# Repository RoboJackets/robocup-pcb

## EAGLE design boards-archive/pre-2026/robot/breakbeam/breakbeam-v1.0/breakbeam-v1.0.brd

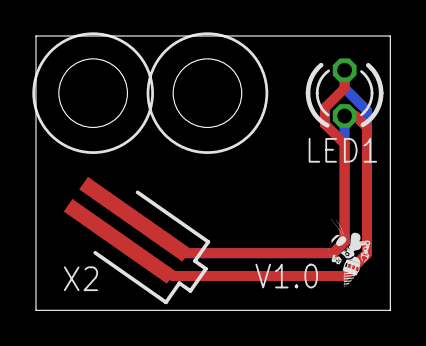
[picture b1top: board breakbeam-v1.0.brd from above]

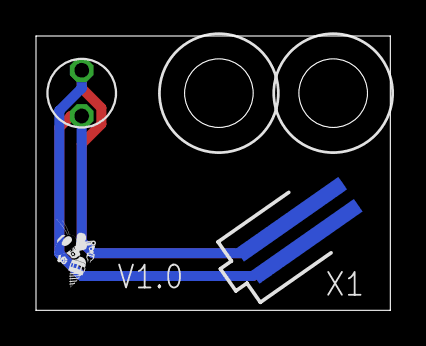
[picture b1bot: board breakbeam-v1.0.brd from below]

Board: 2 copper layers, 19.7 x 15.2 mm, 5 parts (2 on the bottom side), 2 nets.

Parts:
LED1: LED3MM
U$1, U$4: ROBOBUZZ_0.2X
X1, X2: 87438-02

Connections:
unnamed: LED1.A, X1.1, X2.1
unnamed: LED1.K, X1.2, X2.2

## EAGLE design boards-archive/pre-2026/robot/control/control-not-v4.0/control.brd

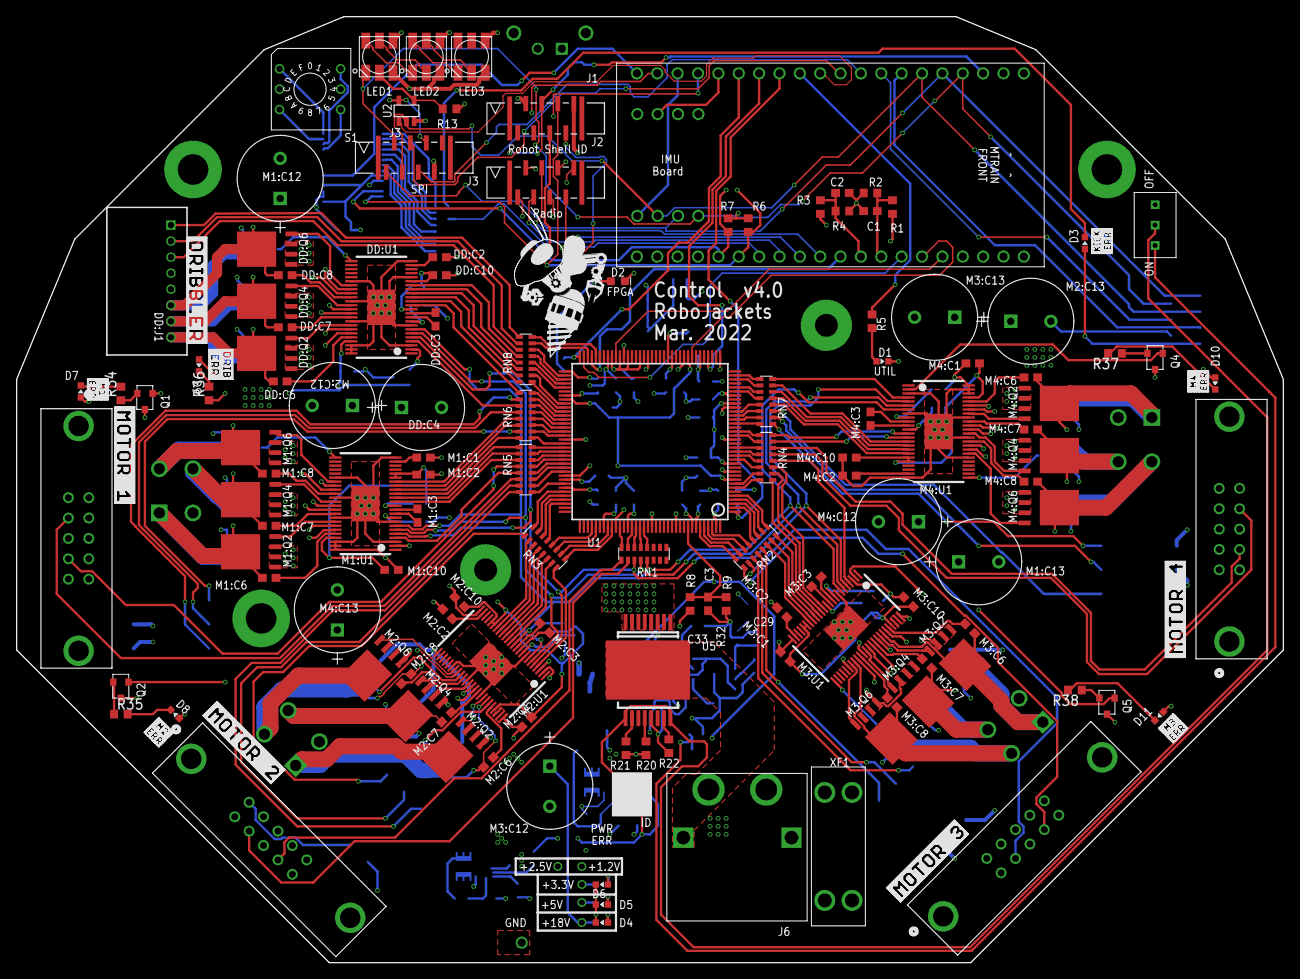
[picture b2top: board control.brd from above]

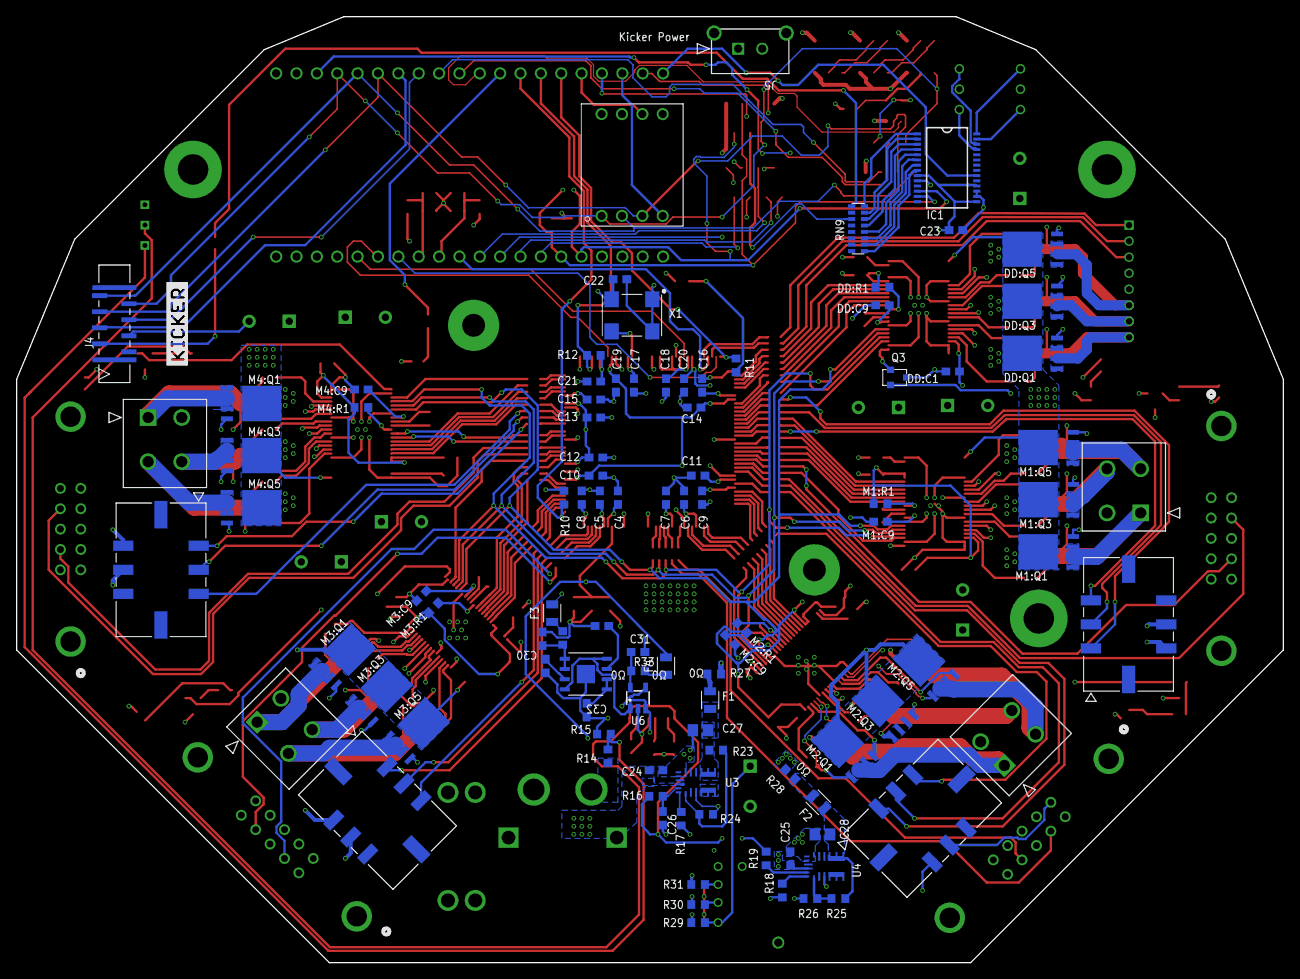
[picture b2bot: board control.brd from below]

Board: 6 copper layers, 158.0 x 118.0 mm, 238 parts (100 on the bottom side), 312 nets.

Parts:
C1: 0.1uF 50V; C0603
C2, C3, C4, C5, C6, C7, C8, C9, C10, C11, C12, C13, C14, C15, C16, C17, C18, C19, C20, C21, C22, C23: 0.1uF; C0603
C24, C25: GRM188R6YA106MA73D; C0603
C26: 2.2uF 50V; C0603
C27, C28: 22uF 16V; C0805
C29: 10uF; C0603
C30, C31, C32, C33: 1uF; C0603
D1: BLUE; CHIP-LED0603
D2: BLUE; LED-0603
D3, D7, D8, D9, D10, D11: RED; CHIP-LED0603
D4, D5, D6: GREEN; CHIP-LED0603
DD:C1, DD:C2: 1uF; C0603
DD:C3: 0.022uF 50V; C0603
DD:C4: ECA-1HHG221; CAP_PAN_10X12.5
DD:C6, DD:C7, DD:C8, DD:C10: 0.1uF 50V; C0603
DD:C9: 2.2uF 50V; C0603
DD:J1: 8-PIN_2MM-H; 2MM-8-H
DD:Q1, DD:Q2, DD:Q3, DD:Q4, DD:Q5, DD:Q6: IRFH7545; PQFN_5X6_E
DD:R1: 10k; R0603
DD:U1: DRV8303DCA; TSSOP-48_PAD
F1, F2, F3, F4: 0805L200SLTHYR; FUSC2113X75
IC1: MCP23017-E/SS; SSOP-28
J1, J2, J3, J4: SFW8S-2STE1LF; CON8_1X8_UB_SFW_JAE
J5: 436500217; CON_436500217_MOL
J6: XT60PW-MAMASS; XT60PW-M
KIT1: MTRAIN; MTRAIN-KIT
KIT2: IMU
LED1, LED2, LED3: APA102C-5050; APA102_5050
M1:C1, M1:C2, M2:C1, M2:C2, M3:C1, M3:C2, M4:C1, M4:C2: 1uF; C0603
M1:C3, M2:C3, M3:C3, M4:C3: 0.022uF 50V; C0603
M1:C6, M1:C7, M1:C8, M1:C10, M2:C6, M2:C7, M2:C8, M2:C10, M3:C6, M3:C7, M3:C8, M3:C10, M4:C6, M4:C7, M4:C8, M4:C10: 0.1uF 50V; C0603
M1:C9, M2:C9, M3:C9, M4:C9: 2.2uF 50V; C0603
M1:C12, M1:C13, M2:C12, M2:C13, M3:C12, M3:C13, M4:C12, M4:C13: ECA-1HHG221; CAP_PAN_10X12.5
M1:J1, M2:J1, M3:J1, M4:J1: 430450618; CON_430450618_MOL
M1:J2, M2:J2, M3:J2, M4:J2: 39288040; CON_39288040
M1:Q1, M1:Q2, M1:Q3, M1:Q4, M1:Q5, M1:Q6, M2:Q1, M2:Q2, M2:Q3, M2:Q4, M2:Q5, M2:Q6, M3:Q1, M3:Q2, M3:Q3, M3:Q4, M3:Q5, M3:Q6, M4:Q1, M4:Q2, M4:Q3, M4:Q4, M4:Q5, M4:Q6: IRFH7545; PQFN_5X6_E
M1:R1, M2:R1, M3:R1, M4:R1: 10k; R0603
M1:U1, M2:U1, M3:U1, M4:U1: DRV8303DCA; TSSOP-48_PAD
M1:U2, M2:U2, M3:U2, M4:U2: N3793-6303RB; N3793-6303RB_3MM
Q1, Q2, Q3, Q4, Q5: PJA3439_R1_00001; SOT-23
R1: 68k 1%; R0603
R2, R3, R4: 10k 1%; R0603
R5, R11: 270; R0603
R6, R7, R10, R12: 4.7k; R0603
R8: 68k; R0603
R9, R20: 10k; R0603
R13: 50k; R0603
R14: 270k; R0603
R15: 100k; R0603
R16, R19: 150k; R0603
R17: 43.2k; R0603
R18: 29.4k; R0603
R21, R22, R29, R30, R31: 1k; R0603
R23, R25: 160k 1%; R0603
R24: 30.1k 1%; R0603
R26: 51.0k 1%; R0603
R27, R28, R32, R33: 0; R0603
R34, R35, R36, R37, R38: 330; R0603
RN1, RN2, RN3, RN4, RN5, RN6, RN7, RN8, RN9: 330; RA-8_2506
S1: 94HCB16T; HEX
S2: TT11EGPC1
U1: XC3S250E-4TQG144C; TQFP144
U2: SN74AHC1G125; SOT-23-5
U3, U4: MPM3620GQV-P
U5: VND5E006ASPTR-E; POWERSO-16
U6: MCP1824T-2502E/OT; SOT-23-5
U7: ADP7158ARDZ-1.2-R7ADP7158ARDZ-1.2-R7_ADI-L; ADP7158ARDZ-1.2-R7_ADI-L
U$1: DRIBBLER
U$2: ERR-KICK
U$3: ERR-DRIB
U$4: ROBOBUZZ_1.0X2
U$5: ERR-M4
U$6: ERR-M1
U$7: MOTOR-1
U$8: MOTOR-4
U$9: MOTOR-2
U$10: ERR-M3
U$11: ERR-M2
U$12: MOTOR-3
U$100: KICKER
X1: ASV-18.432MHZ-EJ-T; ASV
XF1: 30A; 3557-2

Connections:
5V-LED: D5.A, R30.2
5V-LED1: D6.A, R31.2
18.5V-LED: D4.A, R29.1
!CS!-DOT: KIT1.P$11, U2.1
!CS!-FPGA: KIT1.P$31, U1.69
!CS!-ICM: KIT1.P$18, KIT2.4
!CS!-IR: J3.4, KIT1.P$10
!CS!-KICK: J4.5, KIT1.P$8
!CS!-RAD0: J2.5, KIT1.P$17
!RST!-I2C: J1.5, RN9.11
!RST!-IR: J3.5, KIT1.P$9
!RST!-KICK: J4.4, KIT1.P$7
!RST!-RADIO: J2.6, KIT1.P$19
+1.2V: C6.1, C10.1, C14.1, C19.1, F3.2, U1.9, U1.45, U1.80, U1.115
+1.2V-PRE: C29.1, R32.1, U7.1, U7.2
+2.5V: C4.1, C9.1, C15.1, C20.1, F4.2, R10.2, U1.30, U1.65, U1.102, U1.137
+2.5V-PRE: C31.1, R33.1, U6.5
+3.3V: C5.1, C7.1, C8.1, C11.1, C12.1, C13.1, C16.1, C17.1, C18.1, C21.1, C22.1, C23.1, D3.A, D7.A, D8.A, D9.A, D10.A, D11.A, DD:C1.1, DD:C10.1, DD:R1.1, DD:U1.19, DD:U1.45, IC1.9, IC1.15, IC1.18, J3.6, J4.2, KIT2.8, R6.2, R7.2, R12.1, R28.2, R31.1, U1.13, U1.28, U1.42, U1.49, U1.57, U1.60, U1.62, U1.64, U1.79, U1.100, U1.121, U1.138, U1.143, U2.5, U6.1, U6.3, U7.4, U7.8, X1.1, X1.4
+3.3V-FUSE: C28.1, F2.1, R25.2, U4.789
+5V: DD:J1.5, J1.8, J2.1, KIT1.VIN, LED1.1, LED2.1, LED3.1, M1:J1.5, M1:U2.9, M2:J1.5, M2:U2.9, M3:J1.5, M3:U2.9, M4:J1.5, M4:U2.9, R3.1, R27.2, R30.1
+5V-FUSE: C27.1, F1.1, R23.2, U3.789
+18.5V: C24.1, C25.1, DD:C4.1, DD:Q1.5678, DD:Q3.5678, DD:Q5.5678, DD:U1.25, M1:C12.1, M1:C13.1, M1:Q1.5678, M1:Q3.5678, M1:Q5.5678, M1:U1.25, M2:C12.1, M2:C13.1, M2:Q1.5678, M2:Q3.5678, M2:Q5.5678, M2:U1.25, M3:C12.1, M3:C13.1, M3:Q1.5678, M3:Q3.5678, M3:Q5.5678, M3:U1.25, M4:C12.1, M4:C13.1, M4:Q1.5678, M4:Q3.5678, M4:Q5.5678, M4:U1.25, R1.1, R8.1, R29.2, U3.16, U4.16, XF1.3, XF1.4
AAM: R17.2, U3.18
AAM1: R18.2, U4.18
BATT-FPGA: C3.1, R8.2, R9.1, U1.136
BYP: C30.1, U7.3
CS1: R21.2, U5.10
CS2: R22.2, U5.15
CS-DIS: R20.2, U5.12
DD-!CS: DD:U1.4, RN6.11
DD-!FAULT!: DD:U1.2, Q3.1
DD-A-H: DD:U1.13, RN6.9
DD-A-L: DD:U1.14, RN8.16
DD-B-H: DD:U1.15, RN8.15
DD-B-L: DD:U1.16, RN8.14
DD-C-H: DD:U1.17, RN8.13
DD-C-L: DD:U1.18, RN8.12
DD-H1: DD:J1.3, RN8.11
DD-H2: DD:J1.2, RN8.10
DD-H3: DD:J1.1, RN8.9
DD:AVDD: DD:C2.1, DD:U1.23
DD:BST-A: DD:C6.1, DD:U1.44
DD:BST-B: DD:C7.1, DD:U1.39
DD:BST-C: DD:C8.1, DD:U1.34
DD:CP1: DD:C3.1, DD:U1.10
DD:CP2: DD:C3.2, DD:U1.11
DD:EN-GATE: DD:R1.2, DD:U1.12
DD:GH-A: DD:Q1.4, DD:U1.43
DD:GH-B: DD:Q3.4, DD:U1.38
DD:GH-C: DD:Q5.4, DD:U1.33
DD:GL-A: DD:Q2.4, DD:U1.41
DD:GL-B: DD:Q4.4, DD:U1.36
DD:GL-C: DD:Q6.4, DD:U1.31
DD:GVDD: DD:C9.1, DD:U1.9
DD:PHASE-A: DD:C6.2, DD:J1.8, DD:Q1.1, DD:Q1.2, DD:Q1.3, DD:Q2.5678, DD:U1.42
DD:PHASE-B: DD:C7.2, DD:J1.7, DD:Q3.1, DD:Q3.2, DD:Q3.3, DD:Q4.5678, DD:U1.37
DD:PHASE-C: DD:C8.2, DD:J1.6, DD:Q5.1, DD:Q5.2, DD:Q5.3, DD:Q6.5678, DD:U1.32
DOT-CLK-1: LED1.5, R13.2, U2.4
DOT-CLK-1-2: LED1.2, LED2.5
DOT-CLK-2-3: LED2.2, LED3.5
DOT-MOSI-1-2: LED1.3, LED2.4
DOT-MOSI-2-3: LED2.3, LED3.4
EN: C26.1, R16.2, U3.17
EN1: R19.2, U4.17
EN-PWR: R16.1, R19.1, S2.3, U5.9, U5.16
EN-PWR-PRE: R14.1, R15.2, S2.2
EXTRA-IND: KIT1.P$12, R5.1
FB: R23.1, R24.2, U3.1
FB1: R25.1, R26.2, U4.1
FPGA-CLK: U1.50, X1.3
FPGA-DONE: KIT1.P$15, R11.1, U1.72
FPGA-INIT: KIT1.P$14, R12.2, U1.40
FPGA-PROG: KIT1.P$13, R10.1, U1.1
GND: C1.2, C2.2, C3.2, C4.2, C5.2, C6.2, C7.2, C8.2, C9.2, C10.2, C11.2, C12.2, C13.2, C14.2, C15.2, C16.2, C17.2, C18.2, C19.2, C20.2, C21.2, C22.2, C23.2, C24.2, C25.2, C26.2, C27.2, C28.2, C29.2, C30.2, C31.2, C32.2, C33.2, D1.C, D2.C, D4.C, D5.C, D6.C, DD:C1.2, DD:C2.2, DD:C4.2, DD:C9.2, DD:C10.2, DD:J1.4, DD:Q2.1, DD:Q2.2, DD:Q2.3, DD:Q4.1, DD:Q4.2, DD:Q4.3, DD:Q6.1, DD:Q6.2, DD:Q6.3, DD:U1.3, DD:U1.8, DD:U1.20, DD:U1.24, DD:U1.30, DD:U1.35, DD:U1.40, DD:U1.46, DD:U1.47, DD:U1.48, DD:U1.PAD, IC1.10, IC1.16, IC1.17, J1.2, J2.2, J3.7, J4.3, J5.2, J6.P$1, J6.P$3, KIT1.GND, KIT2.5, LED1.6, LED2.6, LED3.6, M1:C1.2, M1:C2.2, M1:C9.2, M1:C10.2, M1:C12.2, M1:C13.2, M1:J1.4, M1:Q2.1, M1:Q2.2, M1:Q2.3, M1:Q4.1, M1:Q4.2, M1:Q4.3, M1:Q6.1, M1:Q6.2, M1:Q6.3, M1:U1.3, M1:U1.8, M1:U1.24, M1:U1.30, M1:U1.35, M1:U1.40, M1:U1.46, M1:U1.47, M1:U1.48, M1:U1.PAD, M1:U2.7, M2:C1.2, M2:C2.2, M2:C9.2, M2:C10.2, M2:C12.2, M2:C13.2, M2:J1.4, M2:Q2.1, M2:Q2.2, M2:Q2.3, M2:Q4.1, M2:Q4.2, M2:Q4.3, M2:Q6.1, M2:Q6.2, M2:Q6.3, M2:U1.3, M2:U1.8, M2:U1.24, M2:U1.30, M2:U1.35, M2:U1.40, M2:U1.46, M2:U1.47, M2:U1.48, M2:U1.PAD, M2:U2.7, M3:C1.2, M3:C2.2, M3:C9.2, M3:C10.2, M3:C12.2, M3:C13.2, M3:J1.4, M3:Q2.1, M3:Q2.2, M3:Q2.3, M3:Q4.1, M3:Q4.2, M3:Q4.3, M3:Q6.1, M3:Q6.2, M3:Q6.3, M3:U1.3, M3:U1.8, M3:U1.24, M3:U1.30, M3:U1.35, M3:U1.40, M3:U1.46, M3:U1.47, M3:U1.48, M3:U1.PAD, M3:U2.7, M4:C1.2, M4:C2.2, M4:C9.2, M4:C10.2, M4:C12.2, M4:C13.2, M4:J1.4, M4:Q2.1, M4:Q2.2, M4:Q2.3, M4:Q4.1, M4:Q4.2, M4:Q4.3, M4:Q6.1, M4:Q6.2, M4:Q6.3, M4:U1.3, M4:U1.8, M4:U1.24, M4:U1.30, M4:U1.35, M4:U1.40, M4:U1.46, M4:U1.47, M4:U1.48, M4:U1.PAD, M4:U2.7, Q1.3, Q2.3, Q3.3, Q4.3, Q5.3, R2.2, R4.2, R9.2, R13.1, R15.1, R17.1, R18.1, R20.1, R21.1, R22.1, R24.1, R26.1, S1.C1, S1.C2, S2.1, U1.11, U1.19, U1.27, U1.37, U1.46, U1.55, U1.61, U1.73, U1.90, U1.99, U1.118, U1.127, U1.133, U2.3, U3.3, U3.12, U3.13, U3.14, U4.3, U4.12, U4.13, U4.14, U5.13, U6.2, U7.EPAD, X1.2
GPB0: IC1.1, RN9.8
GPB1: IC1.2, RN9.7
GPB2: IC1.3, RN9.6
GPB3: IC1.4, RN9.5
GPB4: IC1.5, RN9.4
GPB5: IC1.6, RN9.3
GPB6: IC1.7, RN9.2
GPB7: IC1.8, RN9.1
HEX-0: IC1.28, S1.1
HEX-1: IC1.25, S1.2
HEX-2: IC1.27, S1.4
HEX-3: IC1.26, S1.8
INT-I2C: J1.4, KIT1.P$3
INT-ICM: KIT1.P$16, KIT2.6
INT-IO: IC1.20, KIT1.P$20
INT-RAD0: J2.4, KIT1.P$30
LED-DD: D9.C, R36.2
LED-KICK: D3.C, RN9.9
LED-M1: D7.C, R34.2
LED-M2: D8.C, R35.2
LED-M3: D11.C, R38.2
LED-M4: D10.C, R37.2
M1-!CS: M1:U1.4, RN5.13
M1-!FAULT!: M1:U1.2, Q1.1
M1-A-H: M1:U1.15, RN5.9
M1-A-L: M1:U1.16, RN6.16
M1-B-H: M1:U1.13, RN5.11
M1-B-L: M1:U1.14, RN5.10
M1-C-H: M1:U1.17, RN6.14
M1-C-L: M1:U1.18, RN6.13
M1-ENC-A: M1:U2.8, RN5.14
M1-ENC-B: M1:U2.4, RN5.12
M1-H1: M1:J1.1, RN6.10
M1-H2: M1:J1.2, RN6.12
M1-H3: M1:J1.3, RN6.15
M1:+3.3V: M1:C1.1, M1:C10.1, M1:R1.1, M1:U1.19, M1:U1.20, M1:U1.45
M1:AVDD: M1:C2.1, M1:U1.23
M1:BST-A: M1:C6.1, M1:U1.44
M1:BST-B: M1:C7.1, M1:U1.39
M1:BST-C: M1:C8.1, M1:U1.34
M1:CP1: M1:C3.1, M1:U1.10
M1:CP2: M1:C3.2, M1:U1.11
M1:EN-GATE: M1:R1.2, M1:U1.12
M1:GH-A: M1:Q1.4, M1:U1.43
M1:GH-B: M1:Q3.4, M1:U1.38
M1:GH-C: M1:Q5.4, M1:U1.33
M1:GL-A: M1:Q2.4, M1:U1.41
M1:GL-B: M1:Q4.4, M1:U1.36
M1:GL-C: M1:Q6.4, M1:U1.31
M1:GVDD: M1:C9.1, M1:U1.9
M1:PHASE-A: M1:C7.2, M1:J2.4, M1:Q3.1, M1:Q3.2, M1:Q3.3, M1:Q4.5678, M1:U1.37
M1:PHASE-B: M1:C6.2, M1:J2.1, M1:Q1.1, M1:Q1.2, M1:Q1.3, M1:Q2.5678, M1:U1.42
M1:PHASE-C: M1:C8.2, M1:J2.3, M1:Q5.1, M1:Q5.2, M1:Q5.3, M1:Q6.5678, M1:U1.32
M2-!CS: M2:U1.4, RN3.16
M2-!FAULT!: M2:U1.2, Q2.1
M2-A-H: M2:U1.15, RN3.13
M2-A-L: M2:U1.16, RN3.12
M2-B-H: M2:U1.13, RN3.15
M2-B-L: M2:U1.14, RN3.14
M2-C-H: M2:U1.17, RN3.11
M2-C-L: M2:U1.18, RN3.10
M2-ENC-A: M2:U2.8, RN1.10
M2-ENC-B: M2:U2.4, RN1.9
M2-H1: M2:J1.1, RN5.15
M2-H2: M2:J1.2, RN5.16
M2-H3: M2:J1.3, RN3.9
M2:+3.3V: M2:C1.1, M2:C10.1, M2:R1.1, M2:U1.19, M2:U1.20, M2:U1.45
M2:AVDD: M2:C2.1, M2:U1.23
M2:BST-A: M2:C6.1, M2:U1.44
M2:BST-B: M2:C7.1, M2:U1.39
M2:BST-C: M2:C8.1, M2:U1.34
M2:CP1: M2:C3.1, M2:U1.10
M2:CP2: M2:C3.2, M2:U1.11
M2:EN-GATE: M2:R1.2, M2:U1.12
M2:GH-A: M2:Q1.4, M2:U1.43
M2:GH-B: M2:Q3.4, M2:U1.38
M2:GH-C: M2:Q5.4, M2:U1.33
M2:GL-A: M2:Q2.4, M2:U1.41
M2:GL-B: M2:Q4.4, M2:U1.36
M2:GL-C: M2:Q6.4, M2:U1.31
M2:GVDD: M2:C9.1, M2:U1.9
M2:PHASE-A: M2:C7.2, M2:J2.4, M2:Q3.1, M2:Q3.2, M2:Q3.3, M2:Q4.5678, M2:U1.37
M2:PHASE-B: M2:C6.2, M2:J2.1, M2:Q1.1, M2:Q1.2, M2:Q1.3, M2:Q2.5678, M2:U1.42
M2:PHASE-C: M2:C8.2, M2:J2.3, M2:Q5.1, M2:Q5.2, M2:Q5.3, M2:Q6.5678, M2:U1.32
M3-!CS: M3:U1.4, RN4.12
M3-!FAULT!: M3:U1.2, Q5.1
M3-A-H: M3:U1.15, RN4.9
M3-A-L: M3:U1.16, RN2.16
M3-B-H: M3:U1.13, RN4.11
M3-B-L: M3:U1.14, RN4.10
M3-C-H: M3:U1.17, RN2.15
M3-C-L: M3:U1.18, RN2.14
M3-ENC-A: M3:U2.8, RN2.10
M3-ENC-B: M3:U2.4, RN2.9
M3-H1: M3:J1.1, RN2.11
M3-H2: M3:J1.2, RN2.12
M3-H3: M3:J1.3, RN2.13
M3:+3.3V: M3:C1.1, M3:C10.1, M3:R1.1, M3:U1.19, M3:U1.20, M3:U1.45
M3:AVDD: M3:C2.1, M3:U1.23
M3:BST-A: M3:C6.1, M3:U1.44
M3:BST-B: M3:C7.1, M3:U1.39
M3:BST-C: M3:C8.1, M3:U1.34
M3:CP1: M3:C3.1, M3:U1.10
M3:CP2: M3:C3.2, M3:U1.11
M3:EN-GATE: M3:R1.2, M3:U1.12
M3:GH-A: M3:Q1.4, M3:U1.43
M3:GH-B: M3:Q3.4, M3:U1.38
M3:GH-C: M3:Q5.4, M3:U1.33
M3:GL-A: M3:Q2.4, M3:U1.41
M3:GL-B: M3:Q4.4, M3:U1.36
M3:GL-C: M3:Q6.4, M3:U1.31
M3:GVDD: M3:C9.1, M3:U1.9
M3:PHASE-A: M3:C7.2, M3:J2.4, M3:Q3.1, M3:Q3.2, M3:Q3.3, M3:Q4.5678, M3:U1.37
M3:PHASE-B: M3:C6.2, M3:J2.1, M3:Q1.1, M3:Q1.2, M3:Q1.3, M3:Q2.5678, M3:U1.42
M3:PHASE-C: M3:C8.2, M3:J2.3, M3:Q5.1, M3:Q5.2, M3:Q5.3, M3:Q6.5678, M3:U1.32
M4-!CS: M4:U1.4, RN7.16
M4-!FAULT!: M4:U1.2, Q4.1
M4-A-H: M4:U1.15, RN7.15
M4-A-L: M4:U1.16, RN7.14
M4-B-H: M4:U1.13, RN4.16
M4-B-L: M4:U1.14, RN4.15
M4-C-H: M4:U1.17, RN7.13
M4-C-L: M4:U1.18, RN7.12
M4-ENC-A: M4:U2.8, RN4.14
M4-ENC-B: M4:U2.4, RN4.13
M4-H1: M4:J1.1, RN7.9
M4-H2: M4:J1.2, RN7.10
M4-H3: M4:J1.3, RN7.11
M4:+3.3V: M4:C1.1, M4:C10.1, M4:R1.1, M4:U1.19, M4:U1.20, M4:U1.45
M4:AVDD: M4:C2.1, M4:U1.23
M4:BST-A: M4:C6.1, M4:U1.44
M4:BST-B: M4:C7.1, M4:U1.39
M4:BST-C: M4:C8.1, M4:U1.34
M4:CP1: M4:C3.1, M4:U1.10
M4:CP2: M4:C3.2, M4:U1.11
M4:EN-GATE: M4:R1.2, M4:U1.12
M4:GH-A: M4:Q1.4, M4:U1.43
M4:GH-B: M4:Q3.4, M4:U1.38
M4:GH-C: M4:Q5.4, M4:U1.33
M4:GL-A: M4:Q2.4, M4:U1.41
M4:GL-B: M4:Q4.4, M4:U1.36
M4:GL-C: M4:Q6.4, M4:U1.31
M4:GVDD: M4:C9.1, M4:U1.9
M4:PHASE-A: M4:C7.2, M4:J2.4, M4:Q3.1, M4:Q3.2, M4:Q3.3, M4:Q4.5678, M4:U1.37
M4:PHASE-B: M4:C6.2, M4:J2.1, M4:Q1.1, M4:Q1.2, M4:Q1.3, M4:Q2.5678, M4:U1.42
M4:PHASE-C: M4:C8.2, M4:J2.3, M4:Q5.1, M4:Q5.2, M4:Q5.3, M4:Q6.5678, M4:U1.32
MISO: J3.1, J4.8, KIT1.P$5, KIT2.2
MISO-AUX: DD:U1.6, M1:U1.6, M2:U1.6, M3:U1.6, M4:U1.6, RN1.12
MISO-FPGA: KIT1.P$35, U1.44
MISO-RADIO: J2.3, KIT1.P$28
MOSI: J3.2, J4.7, KIT1.P$4, KIT2.1, LED1.4
MOSI-AUX: DD:U1.5, M1:U1.5, M2:U1.5, M3:U1.5, M4:U1.5, RN1.11
MOSI-FPGA: KIT1.P$36, U1.63
MOSI-RADIO: J2.7, KIT1.P$27
unnamed: F2.2, R28.1
unnamed: F1.2, R27.1
unnamed: F3.1, R32.2
unnamed: F4.1, R33.2
unnamed: D2.A, R11.2
unnamed: D1.A, R5.2
R-D-DD: Q3.2, R36.1
R-D-M1: Q1.2, R34.1
R-D-M2: Q2.2, R35.1
R-D-M3: Q5.2, R38.1
R-D-M4: Q4.2, R37.1
R-P1: RN8.1, U1.82
R-P2: RN8.2, U1.81
R-P3: RN8.3, U1.77
R-P4: RN8.4, U1.76
R-P5: RN8.5, U1.75
R-P6: RN8.6, U1.74
R-P7: RN8.7, U1.70
R-P8: RN8.8, U1.68
R-P9: RN6.1, U1.91
R-P10: RN6.2, U1.89
R-P11: RN6.3, U1.88
R-P12: RN6.4, U1.87
R-P13: RN6.5, U1.86
R-P14: RN6.6, U1.85
R-P15: RN6.7, U1.84
R-P16: RN6.8, U1.83
R-P17: RN5.1, U1.101
R-P18: RN5.2, U1.98
R-P19: RN5.3, U1.97
R-P20: RN5.4, U1.96
R-P21: RN5.5, U1.95
R-P22: RN5.6, U1.94
R-P23: RN5.7, U1.93
R-P24: RN5.8, U1.92
R-P25: RN3.1, U1.117
R-P26: RN3.2, U1.116
R-P27: RN3.3, U1.113
R-P28: RN3.4, U1.112
R-P29: RN3.5, U1.106
R-P30: RN3.6, U1.105
R-P31: RN3.7, U1.104
R-P32: RN3.8, U1.103
R-P36: RN1.4, U1.125
R-P37: RN1.5, U1.124
R-P38: RN1.6, U1.123
R-P39: RN1.7, U1.122
R-P40: RN1.8, U1.119
R-P41: RN2.1, U1.5
R-P42: RN2.2, U1.4
R-P43: RN2.3, U1.3
R-P44: RN2.4, U1.2
R-P45: RN2.5, U1.142
R-P46: RN2.6, U1.141
R-P47: RN2.7, U1.140
R-P48: RN2.8, U1.139
R-P49: RN4.1, U1.21
R-P50: RN4.2, U1.20
R-P51: RN4.3, U1.17
R-P52: RN4.4, U1.16
R-P53: RN4.5, U1.15
R-P54: RN4.6, U1.14
R-P55: RN4.7, U1.8
R-P56: RN4.8, U1.7
R-P57: RN7.1, U1.35
R-P58: RN7.2, U1.34
R-P59: RN7.3, U1.32
R-P60: RN7.4, U1.31
R-P61: RN7.5, U1.26
R-P62: RN7.6, U1.25
R-P63: RN7.7, U1.24
R-P64: RN7.8, U1.23
REF_NET: C32.1, U7.5, U7.6
SCK: J3.3, J4.6, KIT1.P$6, KIT2.3, U2.2
SCK-AUX: DD:U1.7, M1:U1.7, M2:U1.7, M3:U1.7, M4:U1.7, RN1.13
SCK-FPGA: KIT1.P$34, U1.71
SCK-RADIO: J2.8, KIT1.P$29
SCL: IC1.12, J1.7, KIT1.P$25, R7.1
SDA: IC1.13, J1.6, KIT1.P$26, R6.1
SENSE-BATT: C1.1, KIT1.P$33, R1.2, R2.1
SENSE-VIN: C2.1, KIT1.P$32, R3.2, R4.1
VBATT: J5.1, U5.1, U5.2, U5.3, U5.4, U5.5, U5.6, U5.7, U5.8, XF1.1, XF1.2
VIN: J6.P$2, J6.P$4, R14.2, U5.17
VREG: C33.1, U7.7

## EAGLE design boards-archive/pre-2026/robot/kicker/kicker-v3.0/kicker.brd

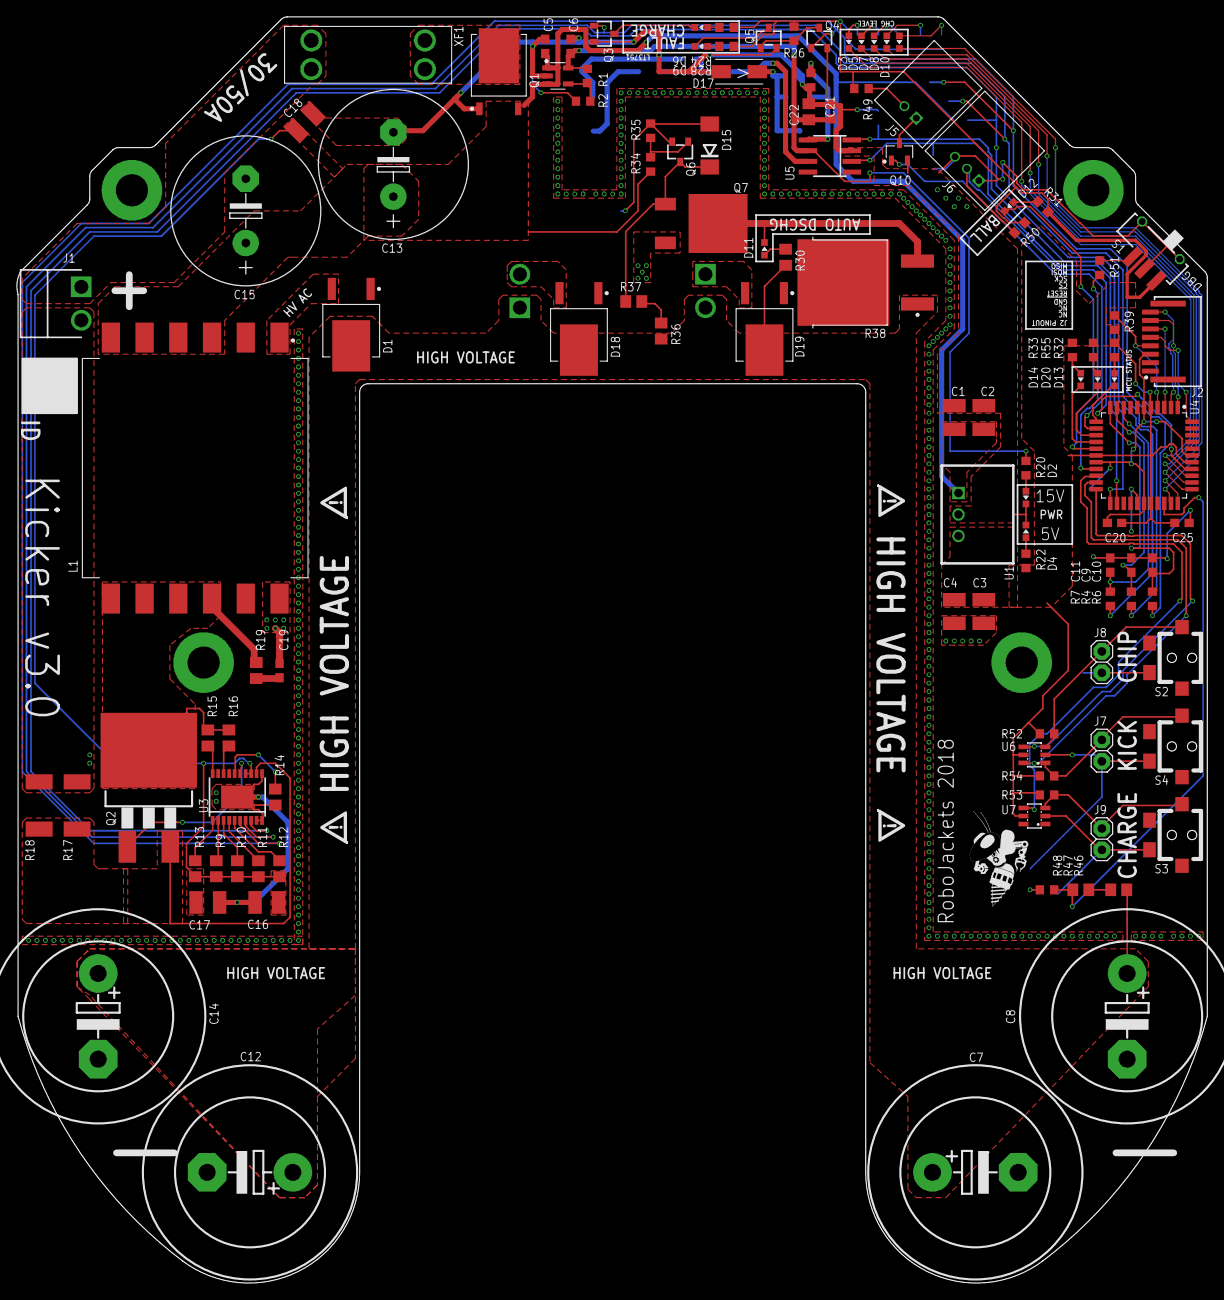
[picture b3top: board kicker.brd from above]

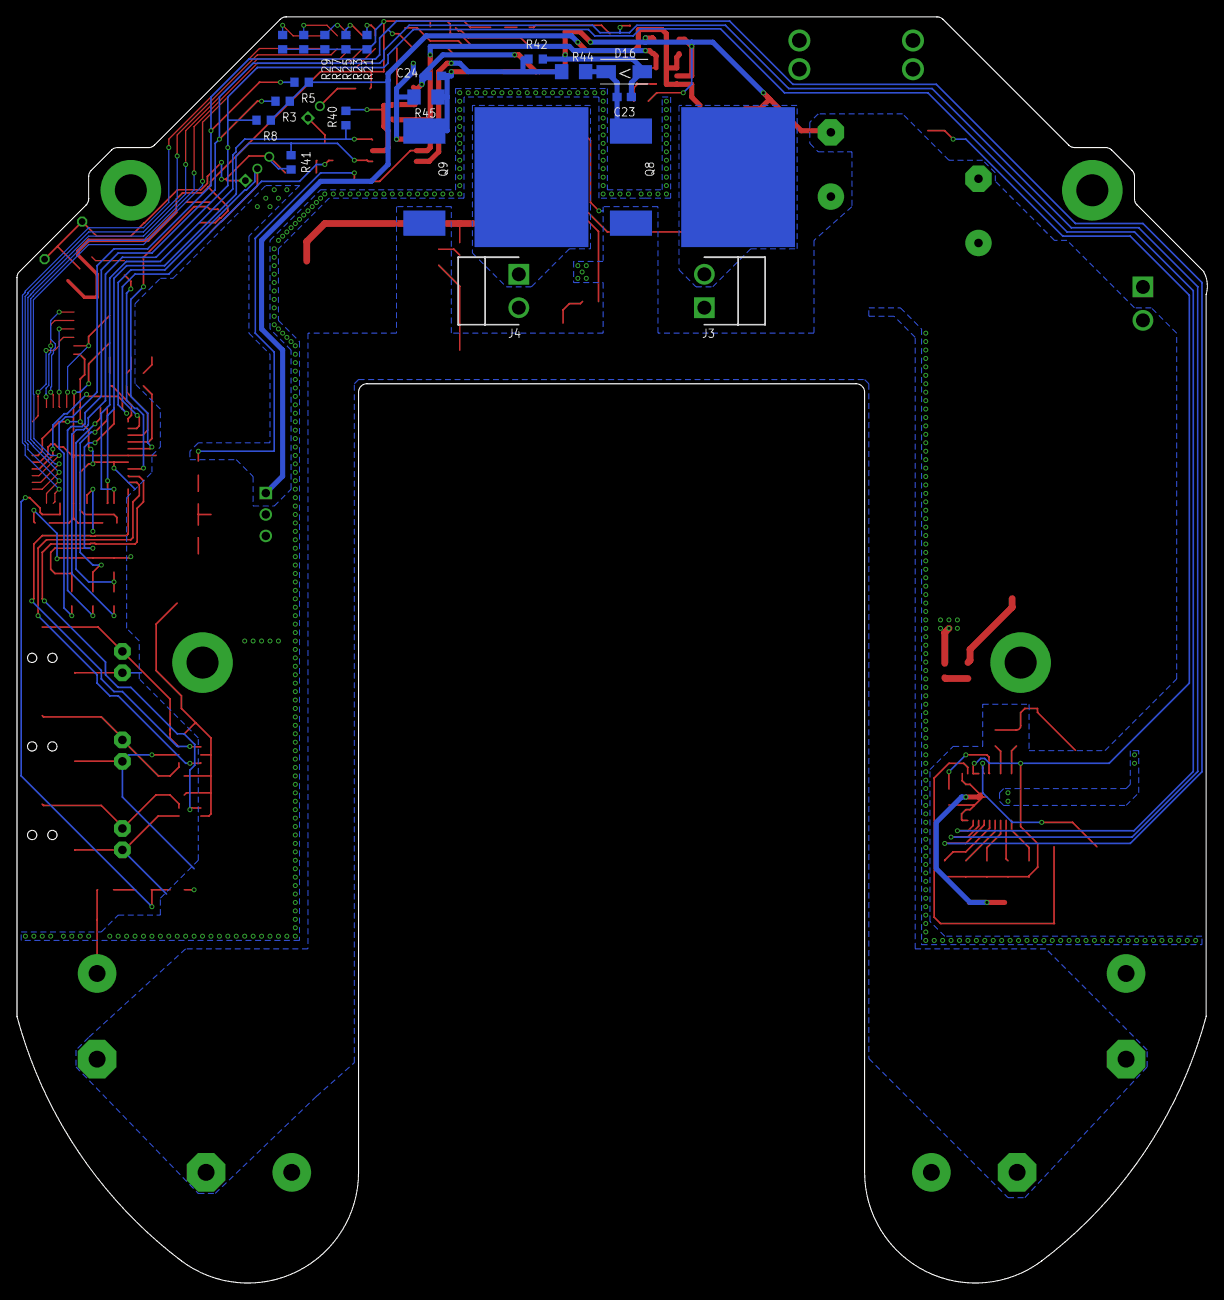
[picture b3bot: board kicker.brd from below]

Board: 2 copper layers, 141.1 x 150.1 mm, 137 parts (20 on the bottom side), 84 nets.

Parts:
C1, C2: 4.7uf 35V; C1210
C3, C4: 4.7uf 16V; C1210
C5, C9, C10, C11: 1uF; C0603
C6: 2.2uF; C0603
C7, C8, C12, C14: 1000uF; EB25D
C13, C15: 560uF; E7,5-18
C16, C17, C18: 10uF (X7R); C1210
C19: 220pF 100V; C0603
C20, C25: 0.1uF; C0603
C21: 0.1uF 35V; C0603
C22: 22uF 35V; C0805
C23, C24: 0.1uF 50V; C0603
D1, D18, D19: VS-5EWH06FN-M3D-PAK_TO252AA; TO460P990X239-3
D2, D3, D4, D5, D6, D13: GREEN; CHIP-LED0603
D7, D11, D20: YELLOW; CHIP-LED0603
D8, D9, D10, D14: RED; CHIP-LED0603
D12: BLUE; CHIP-LED0603
D15: 3SMBJ5929B-TP; DO214AA
D16, D17: SMAJ20ADO-214AC; RESM5226X262
J1, J3, J4: B2PS-VH(LF)(SN); B2PS-CENTERED
J2: HFW8R-1ST
J5: 2-PIN_2MM-H; 2MM-2-H
J6: 3-PIN_2MM-H; 2MM-3-H
J7: !BTN_KCK_PRE_EXT; 1X2
J8: !BTN_CHP_PRE_EXT; 1X2
J9: !BTN_CHG_PRE_EXT; 1X2
L1: GA34XX-BLBL; SOP400P3370X1400-12
Q1: ATP302ATPAK; TO460P950X150-3
Q2: IRFS4227; D2PAK
Q3, Q4, Q5, Q6: BSS127; SOT-23-3
Q7: AOD1N60; DPAK
Q8, Q9: IXFT94N30P3; TO-268
Q10: BSS806NSOT-23-3; SOT95P240X110-3
R1: 110k; R0603
R2, R39, R40, R41, R42, R43, R50, R51, R52, R53, R54: 10k; R0603
R3, R5, R8, R35: 100k; R0603
R4, R6, R7: 160; R0603
R9, R11: 294k 1%; R0805
R10, R12: 412k 1%; R0805
R13, R16: 40.2k 1%; R0805
R14: 1.62k 1%; R0805
R15: 18.2k 1%; R0805
R17, R18: 7.5m 1%; R2512
R19: 22; R0805
R20, R26: 1k; R0603
R21, R22, R23, R24, R32: 162; R0603
R25, R27, R28, R29, R33: 261; R0603
R30: ERJ-P06J274V; R0805
R31, R55: 60; R0603
R34: 270k; R0603
R36, R37, R46, R47: ERJ-6GEYJ515V; R0805
R38: 1.5k 35W; TO508P1539X450-3
R44, R45: 160; R1206
R48: RC0603FR-07205KL; R0603
R49: 50; R0603
S1: CSS-121XB
S2, S3, S4: HDP001R
U1: R-78E5.0-0.5; R-78E
U2: 15V; SOT95P280X145-5
U3: LT3751FE; TSSOP-20_EP
U4: AT32ATQFP44; QFP80P1200X1200X120-44
U5: IX4427N; SOIC-8
U6, U7: MAX6817; SOT-23-6
U$1, U$2, U$3, U$4: WARNING2
U$5: ROBOBUZZ_0.6X
XF1: 30A; 3557-2

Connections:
!BTN_CHG: U4.20, U7.4
!BTN_CHG_PRE: J9.1, R53.1, S3.C, U7.3
!BTN_CHP: U4.22, U6.4
!BTN_CHP_PRE: J8.1, R52.1, S2.C, U6.3
!BTN_KCK: U4.21, U6.6
!BTN_KCK_PRE: J7.1, R54.1, S4.C, U6.1
!DONE!: C9.1, R4.1, U4.10
!DONE_LPF: Q3.1, R3.1, R4.2, U3.7
!FAULT!: C10.1, R6.1, U4.11
!FAULT_LPF: Q4.1, R5.1, R6.2, U3.6
!KICKER_SELECT: J2.5, U4.44
!RESET: J2.4, R39.1, U4.4
+5V: C3.1, C4.1, C20.2, C25.2, R21.2, R22.2, R23.2, R24.2, R25.2, R26.2, R27.2, R28.2, R29.2, R31.2, R32.2, R33.2, R39.2, R49.1, R50.2, R52.2, R53.2, R54.2, R55.2, S1.1, U1.3, U4.5, U4.17, U4.27, U4.29, U4.38, U6.5, U7.5
+15.0V: C6.1, C21.2, C22.2, R1.2, R20.2, U2.5, U5.6
BALL_SENSE: D12.C, U4.16
BB_RX: J6.2, R50.1, U4.37
BB_TX: Q10.1, U4.13
CHARGE: C11.1, R7.1, U4.9
CHARGE_LPF: R7.2, R8.1, U3.8
CHIP: R41.2, U4.24, U5.2
CHIPPER: D18.2, J3.2, Q8.4
CHIP_GATE: R42.2, R44.1, U5.7
DISCHARGE_DRAIN: D11.C, Q7.FIN, R38.2
GND: C1.2, C2.2, C3.2, C4.2, C5.2, C6.2, C7.-, C8.-, C9.2, C10.2, C11.2, C12.-, C13.-, C14.-, C15.-, C16.1, C17.1, C18.1, C19.2, C20.1, C21.1, C22.1, C23.2, C24.2, C25.1, D2.C, D4.C, D15.A, D16.1, D17.1, J1.2, J2.3, J6.1, J6.3, J7.2, J8.2, J9.2, L1.12, Q1.1, Q3.2, Q4.2, Q5.2, Q6.2, Q7.3, Q8.3, Q9.3, Q10.2, R2.1, R14.2, R17.1, R18.1, R35.1, R40.1, R41.1, R42.1, R43.1, R48.1, S1.2, S1.LEG1, S1.LEG4, S2.B, S3.B, S4.B, U1.2, U2.2, U3.9, U3.10, U3.11, U3.PAD, U4.6, U4.18, U4.28, U4.39, U5.3, U6.2, U7.2
HVGATE: Q2.1, U3.15
HV_AC: D1.2, L1.1
HV_IND_HIGH: D8.C, U4.33
HV_IND_LOW: D5.C, U4.35
HV_IND_MAX: D10.C, U4.32
HV_IND_MID: D7.C, U4.34
HV_IND_MIN: D3.C, U4.36
KICK: R40.2, U4.23, U5.4
KICKER: D19.2, J4.1, Q9.4
KICK_GATE: R43.2, R45.1, U5.5
MCU_ERR: D14.C, U4.15
MCU_INIT_OK: D13.C, U4.12
MCU_MODE: D20.C, U4.14
MISO: J2.8, U4.2
MODE_SELECT: R51.2, U4.19
MOSI: J2.7, U4.1
unnamed: R14.1, U3.16
unnamed: R36.1, R37.2
unnamed: D14.A, R33.1
unnamed: D13.A, R32.1
unnamed: D6.A, R24.1
unnamed: J5.2, R49.2
unnamed: C23.1, D16.2, Q8.1, R44.2
unnamed: C24.1, D17.2, Q9.1, R45.2
unnamed: Q1.3, XF1.3, XF1.4
unnamed: Q6.1, R34.1, R35.2
unnamed: D3.A, R21.1
unnamed: D5.A, R23.1
unnamed: D7.A, R25.1
unnamed: R51.1, S1.3
unnamed: R46.1, R47.2
unnamed: R1.1, R2.2, U2.4
unnamed: D20.A, R55.1
unnamed: J5.1, Q10.3
unnamed: D4.A, R22.1
unnamed: D8.A, R27.1
unnamed: D2.A, R20.1
unnamed: R13.1, U3.1
unnamed: Q4.3, Q5.1, R26.1
unnamed: D9.A, R28.1
unnamed: D9.C, Q5.3
unnamed: D11.A, R30.1
unnamed: D10.A, R29.1
unnamed: C19.1, R19.1
unnamed: D6.C, Q3.3
unnamed: J1.1, XF1.1, XF1.2
unnamed: D12.A, R31.1
OVLO1: R10.2, U3.3
OVLO2: R12.2, U3.5
QUICK_DISCHARGE: D15.C, Q6.3, Q7.1, R37.1
RDCM: R15.2, U3.20
RVOUT: R16.2, U3.18
SCK: J2.6, U4.3
SENSE: Q2.3, R17.2, R18.2, U3.12
UVLO1: R9.2, U3.2
UVLO2: R11.2, U3.4
V+: C7.+, C8.+, C12.+, C14.+, D1.3, D18.3, D19.3, J3.1, J4.2, R30.2, R36.2, R38.1, R46.2
VBATT: C1.1, C2.1, C5.1, C13.+, C15.+, C16.2, C17.2, C18.2, L1.3, L1.4, L1.5, L1.6, Q1.2, R3.2, R5.2, R8.2, R9.1, R10.1, R11.1, R12.1, R13.2, R34.2, U1.1, U2.1, U2.3, U3.13, U3.14
VMON: R47.1, R48.2, U4.31
VSN: L1.7, L1.8, L1.9, L1.10, Q2.2, R15.1, R16.1, R19.2

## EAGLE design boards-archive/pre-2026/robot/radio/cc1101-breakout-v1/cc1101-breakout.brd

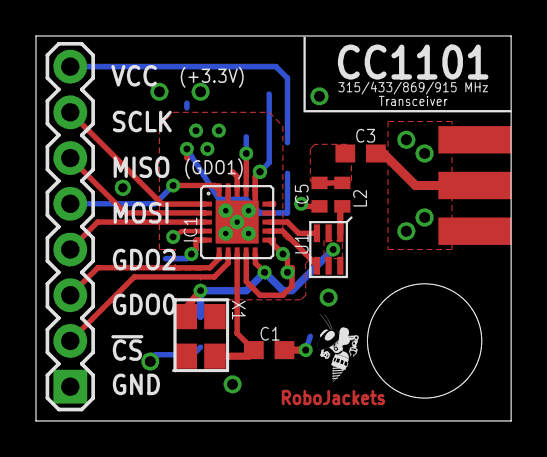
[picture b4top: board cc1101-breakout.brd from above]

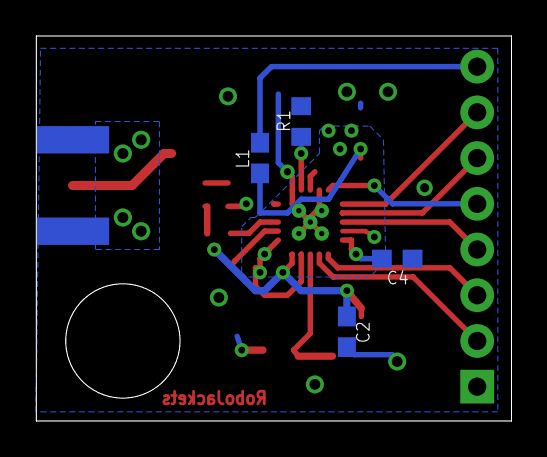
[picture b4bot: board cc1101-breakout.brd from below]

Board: 4 copper layers, 26.4 x 21.4 mm, 14 parts (4 on the bottom side), 18 nets.

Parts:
C1, C2, C3, C4: C0603
C5: C0402
IC1: CC1101; QLP20
J$1: SMA_EDGE; SMA-EDGE
JP2: 1X08
L1: C0603
L2: C0402
R1: 56k; R0603
U1: 0896BM15A0001
U$1: ROBOBUZZ_0.2X
X1: XTAL-3.2X2.5

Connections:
GND: C1.2, C2.2, C4.2, C5.2, IC1.16, IC1.19, IC1.GND, IC1.GND1, IC1.GND2, IC1.GND3, IC1.GND4, IC1.GND5, J$1.GND@0, J$1.GND@1, J$1.GND@2, J$1.GND@3, JP2.1, R1.2
unnamed: IC1.12, U1.4
unnamed: IC1.13, U1.3
unnamed: IC1.1, JP2.7
unnamed: C1.1, IC1.8, X1.1
unnamed: C2.1, IC1.10, U1.2, U1.5, U1.6, X1.3
unnamed: IC1.17, R1.1
unnamed: IC1.2, JP2.6
unnamed: IC1.20, JP2.5
unnamed: L2.1, U1.1
unnamed: IC1.3, JP2.4
unnamed: IC1.6, JP2.3
unnamed: IC1.7, JP2.2
unnamed: C4.1, IC1.5
unnamed: C3.1, C5.1, L2.2
unnamed: C3.2, J$1.SIG
unnamed: IC1.4, IC1.9, IC1.11, IC1.14, IC1.15, IC1.18, L1.1
VCC: JP2.8, L1.2

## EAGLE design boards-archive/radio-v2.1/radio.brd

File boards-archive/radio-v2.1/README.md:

# Radio Board

Board containing radio circuitry to communicate between robot(s) and base station

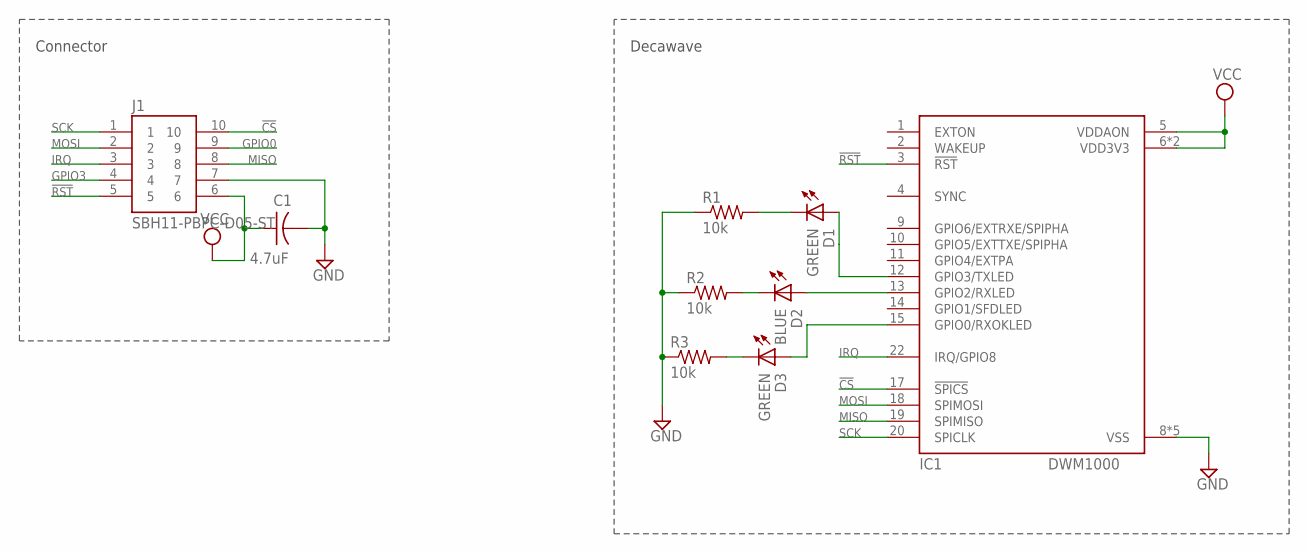
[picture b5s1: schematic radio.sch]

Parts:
C1: 4.7uF; C0603
D1, D3: GREEN; CHIP-LED0603
D2: BLUE; CHIP-LED0603
IC1: DWM1000
J1: SBH11-PBPC-D05-ST; SFH11-*-D05-ST
R1, R2, R3: 10k; R0603

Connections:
!CS: IC1.17 (!SPICS), J1.10
!RST: IC1.3 (!RST), J1.5
GND: C1.2, IC1.8 (VSS), IC1.16 (VSS), IC1.21 (VSS), IC1.23 (VSS), IC1.24 (VSS), J1.7, R1.1, R2.1, R3.1
GPIO0: J1.9
GPIO3: J1.4
IRQ: IC1.22 (IRQ/GPIO8), J1.3
LED-RX: D2.A, IC1.13 (GPIO2/RXLED)
LED-RX-PRE: D2.C (K), R2.2
LED-RXOK: D3.A, IC1.15 (GPIO0/RXOKLED)
LED-RXOK-PRE: D3.C (K), R3.2
LED-TX: D1.A, IC1.12 (GPIO3/TXLED)
LED-TX-PRE: D1.C (K), R1.2
MISO: IC1.19 (SPIMISO), J1.8
MOSI: IC1.18 (SPIMOSI), J1.2
SCK: IC1.20 (SPICLK), J1.1
VCC: C1.1, IC1.5 (VDDAON), IC1.6 (VDD3V3), IC1.7 (VDD3V3), J1.6

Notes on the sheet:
Connector
Decawave

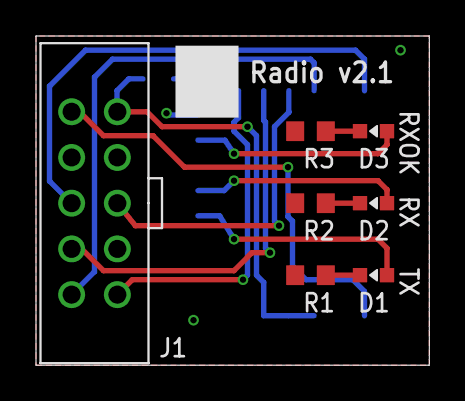
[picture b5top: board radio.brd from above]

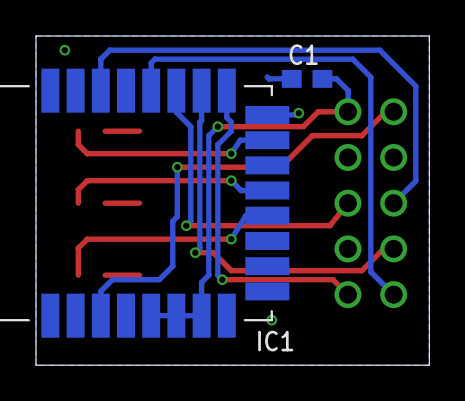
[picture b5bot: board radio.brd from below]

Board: 2 copper layers, 21.9 x 18.3 mm, 9 parts (2 on the bottom side), 14 nets.

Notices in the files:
parts and their libraries:
COPYRIGHT: Copyright (C) 2022 Ultra Librarian. All rights reserved.
SparkFun-Connectors: Licensing: Creative Commons ShareAlike 4.0 International - https://creativecommons.org/licenses/by-sa/4.0
